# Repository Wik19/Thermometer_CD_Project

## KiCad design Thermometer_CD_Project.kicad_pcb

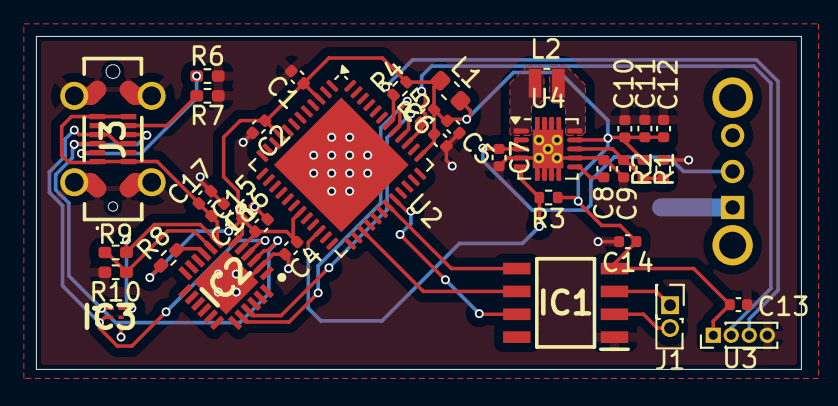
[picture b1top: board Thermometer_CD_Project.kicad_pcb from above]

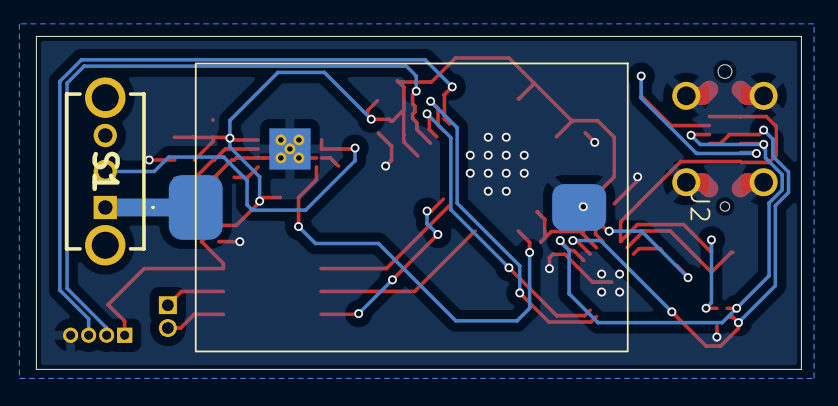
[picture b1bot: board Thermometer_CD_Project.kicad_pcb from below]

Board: 2 copper layers, 42.5 x 18.5 mm, 39 parts (2 on the bottom side), 25 nets.

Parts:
C1, C2, C4, C5, C6, C13, C14: 100nF; C_0402_1005Metric
C7, C10, C11, C12: 22u; C_0402_1005Metric
C8, C15, C18: 0.1u; C_0402_1005Metric
C9: 10p; C_0402_1005Metric
C16, C17: 4.7u; C_0402_1005Metric
IC1: MAX6675ISA+; SOIC127P600X175-8N
IC2: CP2102N-A02-GQFN24; QFN50P400X400X80-25N-D
IC3: TPD4S012DRYR
J1: Screw_Terminal_01x02; PinHeader_2x01_P1.27mm_Vertical
J2: S8421-45R; battery_holder_S8421-custom
J3: UJ20-C-V-C-1-SMT-TR; UJ20CVC1SMTTR
L1: 10u; L_0603_1608Metric
L2: 1u; L_Wuerth_WE-TPC-3816
R1: 560k; R_0402_1005Metric
R2: 100k; R_0402_1005Metric
R3: 1M; R_0402_1005Metric
R4, R5: 4k7; R_0402_1005Metric
R6, R7: 5.1k; R_0402_1005Metric_Pad0.72x0.64mm_HandSolder
R8: 1k; R_0402_1005Metric_Pad0.72x0.64mm_HandSolder
R9: 22.1k; R_0402_1005Metric_Pad0.72x0.64mm_HandSolder
R10: 47.5k; R_0402_1005Metric_Pad0.72x0.64mm_HandSolder
S1: OS102011MS2QS1
U2: ESP32-PICO-D4; QFN-48-1EP_7x7mm_P0.5mm_EP5.3x5.3mm
U3: OLED-disp; PinHeader_1x04_P1.00mm_Vertical
U4: TPS63060; Texas_S-PWSON-N10_ThermalVias

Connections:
+3V3: C1.1, C2.1, C4.1, C5.1, C6.2, C10.1, C11.1, C12.1, C13.1, C14.1, C15.1, C16.1, IC1.4 (VCC), IC2.5 (VIO), IC2.6 (VDD), L1.1, L1.2, R1.1, R3.1, R4.1, R5.1, R8.1, U2.3 (VDDA3P3), U2.9 (EN), U2.19 (VDD3P3_RTC), U2.37 (VDD3P3_CPU), U3.1 (VDD), U4.9 (VOUT)
/CLK: IC1.5 (SCK), U2.31 (CLK)
/CS: IC1.6 (~CS), U2.27 (IO17)
/MAX_SO: IC1.7 (SO), U2.32 (SD0)
/PwrG: R3.2, U2.22 (IO2), U4.5 (PG)
/RXD_USB: IC2.20 (RXD), U2.41 (U0TXD/IO1)
/TXD_USB: IC2.21 (TXD), U2.40 (U0RXD/IO3)
/connectors/D+: IC2.3 (D+), IC3.1 (D+), J3.A6 (DP1), J3.B6 (DP2)
/connectors/D-: IC2.4 (D-), IC3.2 (D-_), J3.A7 (DN1), J3.B7 (DN2)
/thermocouple/T+: IC1.3 (T+), J1.1
/thermocouple/T-: IC1.2 (T-), J1.2
GND: C1.2, C2.2, C4.2, C5.2, C6.1, C7.2, C8.2, C9.2, C10.2, C11.2, C12.2, C13.2, C14.2, C15.2, C16.2, C17.2, C18.2, IC1.1 (GND), IC2.2 (GND_1), IC2.25 (GND_2), IC3.4 (GND), J2.2, J3.1 (MH1), J3.2 (MH2), J3.3 (MH3), J3.4 (MH4), J3.A1 (GND_1), J3.A12 (GND_2), J3.B1 (GND_3), J3.B12 (GND_4), R2.2, R6.1, R7.1, R10.2, U2.49 (GND), U3.4 (GND), U4.4 (PS/SYNC), U4.7 (GND), U4.11 (PGND)
unnamed: IC2.9 (RSTB), R8.2
unnamed: IC2.8 (VBUS), R9.2, R10.1
unnamed: J3.A5 (CC1), R6.2
unnamed: J3.B5 (CC2), R7.2
unnamed: C7.1, S1.2 (COM), U4.2 (VIN), U4.3 (EN)
unnamed: J2.1, S1.1 (NO)
unnamed: R4.2, U2.42 (IO21), U3.3 (SDA)
unnamed: R5.2, U2.39 (IO22), U3.2 (SCL)
unnamed: C9.1, R1.2, R2.1, U4.8 (FB)
unnamed: L2.1, U4.1 (L1)
unnamed: L2.2, U4.10 (L2)
unnamed: C8.1, U4.6 (VAUX)
VBUS: C17.1, C18.1, IC2.7 (VREGIN), IC3.6 (VBUS), J3.A4 (VBUS_1), J3.A9 (VBUS_2), J3.B4 (VBUS_3), J3.B9 (VBUS_4), R9.1

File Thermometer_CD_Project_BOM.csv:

,,,,,,,,,,,,,,,,
,,,,,,,,,,,,,,,,
,,,,,,,,,,,,,,,,
,,,,,,,,,,,,,,,,
,,,,,,,,,,,,,,,,
,,No,Reference,Qty,Value,Name,Footprint,Description,Vendor,Unit price (1 pc.),Price (1 PCB),Unit price (10 pcs.),Price (10 PCB),Unit price (100 pcs.),Price (100 PCB),Link
,,1,"C1,C2,C3,C4,C5,C6,C13,C14",8,100nF,C,Capacitor_SMD:C_0402_1005Metric,unpolarized capacitor,mouser,"1,55","12,4","1,02","81,6","0,615",492,0402X7R104KT2AT KYOCERA AVX | Mouser Polska
,,2,"C7,C10,C11,C12",4,22u,C,Capacitor_SMD:C_0402_1005Metric,unpolarized capacitor,mouser,"2,45","9,8","1,67","66,8","1,1",440,04024W226MAT2A KYOCERA AVX | Mouser Polska
,,3,"C8,C15,C18",3,0.1u,C,Capacitor_SMD:C_0402_1005Metric,unpolarized capacitor,mouser,"1,55","4,65","1,02","30,6","0,615","184,5",0402X7R104KT2AT KYOCERA AVX | Mouser Polska
,,4,C9,1,10p,C,Capacitor_SMD:C_0402_1005Metric,unpolarized capacitor,mouser,"0,452","0,452","0,185","1,85","0,12",12,VJ0402A100KXAPW1BC Vishay / Vitramon | Mouser Polska
,,5,"C16,C17",2,4.7u,C,Capacitor_SMD:C_0402_1005Metric,unpolarized capacitor,mouser,"0,86","1,72","0,581","11,62","0,292","58,4",C0402C475K8PACTU KEMET | Mouser Polska
,,6,IC1,1,MAX6675ISA+,MAX6675ISA+,MAX6675ISA+:SOIC127P600X175-8N,Thermocouple to Digital Converter,mouser,"62,22","62,22","55,3",553,"51,99",5199,MAX6675ISA+ Analog Devices / Maxim Integrated | Mouser Polska
,,7,IC2,1,CP2102N-A02-GQFN24,CP2102N-A02-GQFN24,QFN50P400X400X80-25N-D,USB-to-UART bridge IC,mouser,"18,15","18,15","10,75","107,5","9,85",985,CP2102N-A02-GQFN24 Silicon Labs | Mouser Polska
,,8,IC3,1,TPD4S012DRYR,TPD4S012DRYR,TPD4S012DRYR,ESD Protection Diode,mouser,"2,82","2,82","1,88","18,8","1,29",129,TPD4S012DRYR Texas Instruments | Mouser Polska
,,9,J1,1,Screw_Terminal_01x02,Screw_Terminal_01x02,Connector_PinHeader_1.27mm:PinHeader_2x01_P1.27mm_Vertical,screw terminal,mouser,"2,37","2,37","0,864","8,64","0,679","67,9",TB001-500-02BE Same Sky | Mouser Polska
,,10,J2,1,S8421-45R,S8421-45R,S8421-45R:battery_holder_S8421-custom,battery holder,mouser,"6,58","6,58","4,82","48,2","4,25",425,S8421-45R Harwin | Mouser Polska
,,11,J3,1,UJ20-C-V-C-1-SMT-TR,UJ20-C-V-C-1-SMT-TR,UJ20-C-V-C-1-SMT-TR:UJ20CVC1SMTTR,USB Connector Type C,mouser,"5,68","5,68","4,77","47,7","4,34",434,UJ20-C-H-G-SMT-TR Same Sky | Mouser Polska
,,12,L1,1,10u,L,Inductor_SMD:L_0603_1608Metric,inductor,mouser,"0,409","0,409","0,374","3,74","0,267","26,7",MLZ1608E100MT TDK | Mouser Polska
,,13,L2,1,1u,L,Inductor_SMD:L_Wuerth_WE-TPC-3816,inductor,farnell,"5,34","5,34","5,34","53,4","4,38",438,"744031010 WURTH ELEKTRONIK, Cewka mocy (SMD), 1 µH, 2 A, Osłonięte, 1.6 A, WE-TPC Series | Farnell Polski"
,,14,R1,1,560k,R,Resistor_SMD:R_0402_1005Metric,resistor,mouser,"0,409","0,409","0,056","0,56","0,039","3,9",CRCW0402560KFKED Vishay / Dale | Mouser Polska
,,15,R2,1,100k,R,Resistor_SMD:R_0402_1005Metric,resistor,mouser,"0,409","0,409","0,069","0,69","0,043","4,3",CRCW0402100KFKED Vishay / Dale | Mouser Polska
,,16,R3,1,1M,R,Resistor_SMD:R_0402_1005Metric,resistor,mouser,"0,697","0,697","0,456","4,56","0,176","17,6",CRCW04021M00JNTD Vishay / Dale | Mouser Polska
,,17,"R4,R5",2,4k7,R,Resistor_SMD:R_0402_1005Metric,resistor,mouser,"0,409","0,818","0,06","1,2","0,043","8,6",CRCW04024K70FKED Vishay / Dale | Mouser Polska
,,18,"R6,R7",2,5.1k,R,Resistor_SMD:R_0402_1005Metric_Pad0.72x0.64mm_HandSolder,resistor,mouser,"0,697","1,394","0,456","9,12","0,176","35,2",CRCW04025K10JNTD Vishay / Dale | Mouser Polska
,,19,R8,1,1k,R,Resistor_SMD:R_0402_1005Metric_Pad0.72x0.64mm_HandSolder,resistor,mouser,"1,27","1,27","1,03","10,3","0,404","40,4",CRCW04021K00FHTDP Vishay / Dale | Mouser Polska
,,20,R9,1,22.1k,R,Resistor_SMD:R_0402_1005Metric_Pad0.72x0.64mm_HandSolder,resistor,mouser,"0,409","0,409","0,069","0,69","0,043","4,3",CRCW040222K1FKED Vishay / Dale | Mouser Polska
,,21,R10,1,47.5k,R,Resistor_SMD:R_0402_1005Metric_Pad0.72x0.64mm_HandSolder,resistor,mouser,"0,409","0,409","0,069","0,69","0,039","3,9",CRCW040247K5FKED Vishay / Dale | Mouser Polska
,,22,S1,1,OS102011MS2QS1,OS102011MS2QS1,KiCad:OS102011MS2QS1,Slide Switch SPDT On-On,mouser,"2,33","2,33","1,85","18,5","1,51",151,OS102011MS2QS1 C&K | Mouser Polska
,,23,U2,1,ESP32-PICO-D4,ESP32-PICO-D4,Package_DFN_QFN:QFN-48-1EP_7x7mm_P0.5mm_EP5.3x5.3mm,MCU,mouser,"18,4","18,4","18,4",184,"18,4",1840,ESP32-PICO-D4 Espressif Systems | Mouser Polska
,,24,U3,1,OLED-disp,OLED-disp,Connector_PinHeader_1.00mm:PinHeader_1x04_P1.00mm_Vertical,Oled display,mouser,"27,61","27,61","27,61","276,1","27,61",2761,CS-ANAVI-DISPLAY-1 ANAVI Technology | Mouser Polska
,,25,U4,1,TPS63060,TPS63060,Package_SON:Texas_S-PWSON-N10_ThermalVias,Buck-Boost Converter,mouser,"7,05","7,05","5,63","56,3","5,33",533,TPS63060DSCR Texas Instruments | Mouser Polska
,,,,,,,,,,,,,,,,
,,,,,,,,,,Total (1),For 1 PCB,Total (10),For 1 PCB,Total (100),For 1 PCB,
,,,,,,,,,Total cost of components ,"193,796","193,796","1596,16","159,616","14294,7","142,947",
,,,,,,,*Minimal order of PCB boards is 5,,Cost of manufacturing,"13,25","13,25","26,09","2,609","78,7","0,787",
,,,,,,,**there is no discount when ordering 10 or 100 pcs. of ESP32 and OLED display,,Total cost ,"207,046","207,046","1622,25","162,225","14373,4","143,734",

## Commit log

2024-11-28 Project upload on github
2024-12-01 Added switch and a couple of minor corrections
2024-12-04 Started the PCB layout
2024-12-15 Added partial PCB layout
2024-12-18 PCB design update (mostly capacitors and resistors)
2024-12-18 Another changes in design of PCB
2025-01-09 added USB interface and updated PCB
2025-01-17 changed usb-c connector and a couple of minor changes at the positioning of the other components
2025-01-19 removed errors
2025-01-20 added gerber files and pdf schematic, also modified the schematic
2025-01-20 added BOM
